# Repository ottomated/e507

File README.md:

- [Part choices & planning](./docs/Parts.md)

- Datasheets, symbols, footprints, 3d models, and spice models are in the respective folders in `./parts`

## Schematics

### Power

### MCU

### Audio

### Root

## PCB

### Rendered

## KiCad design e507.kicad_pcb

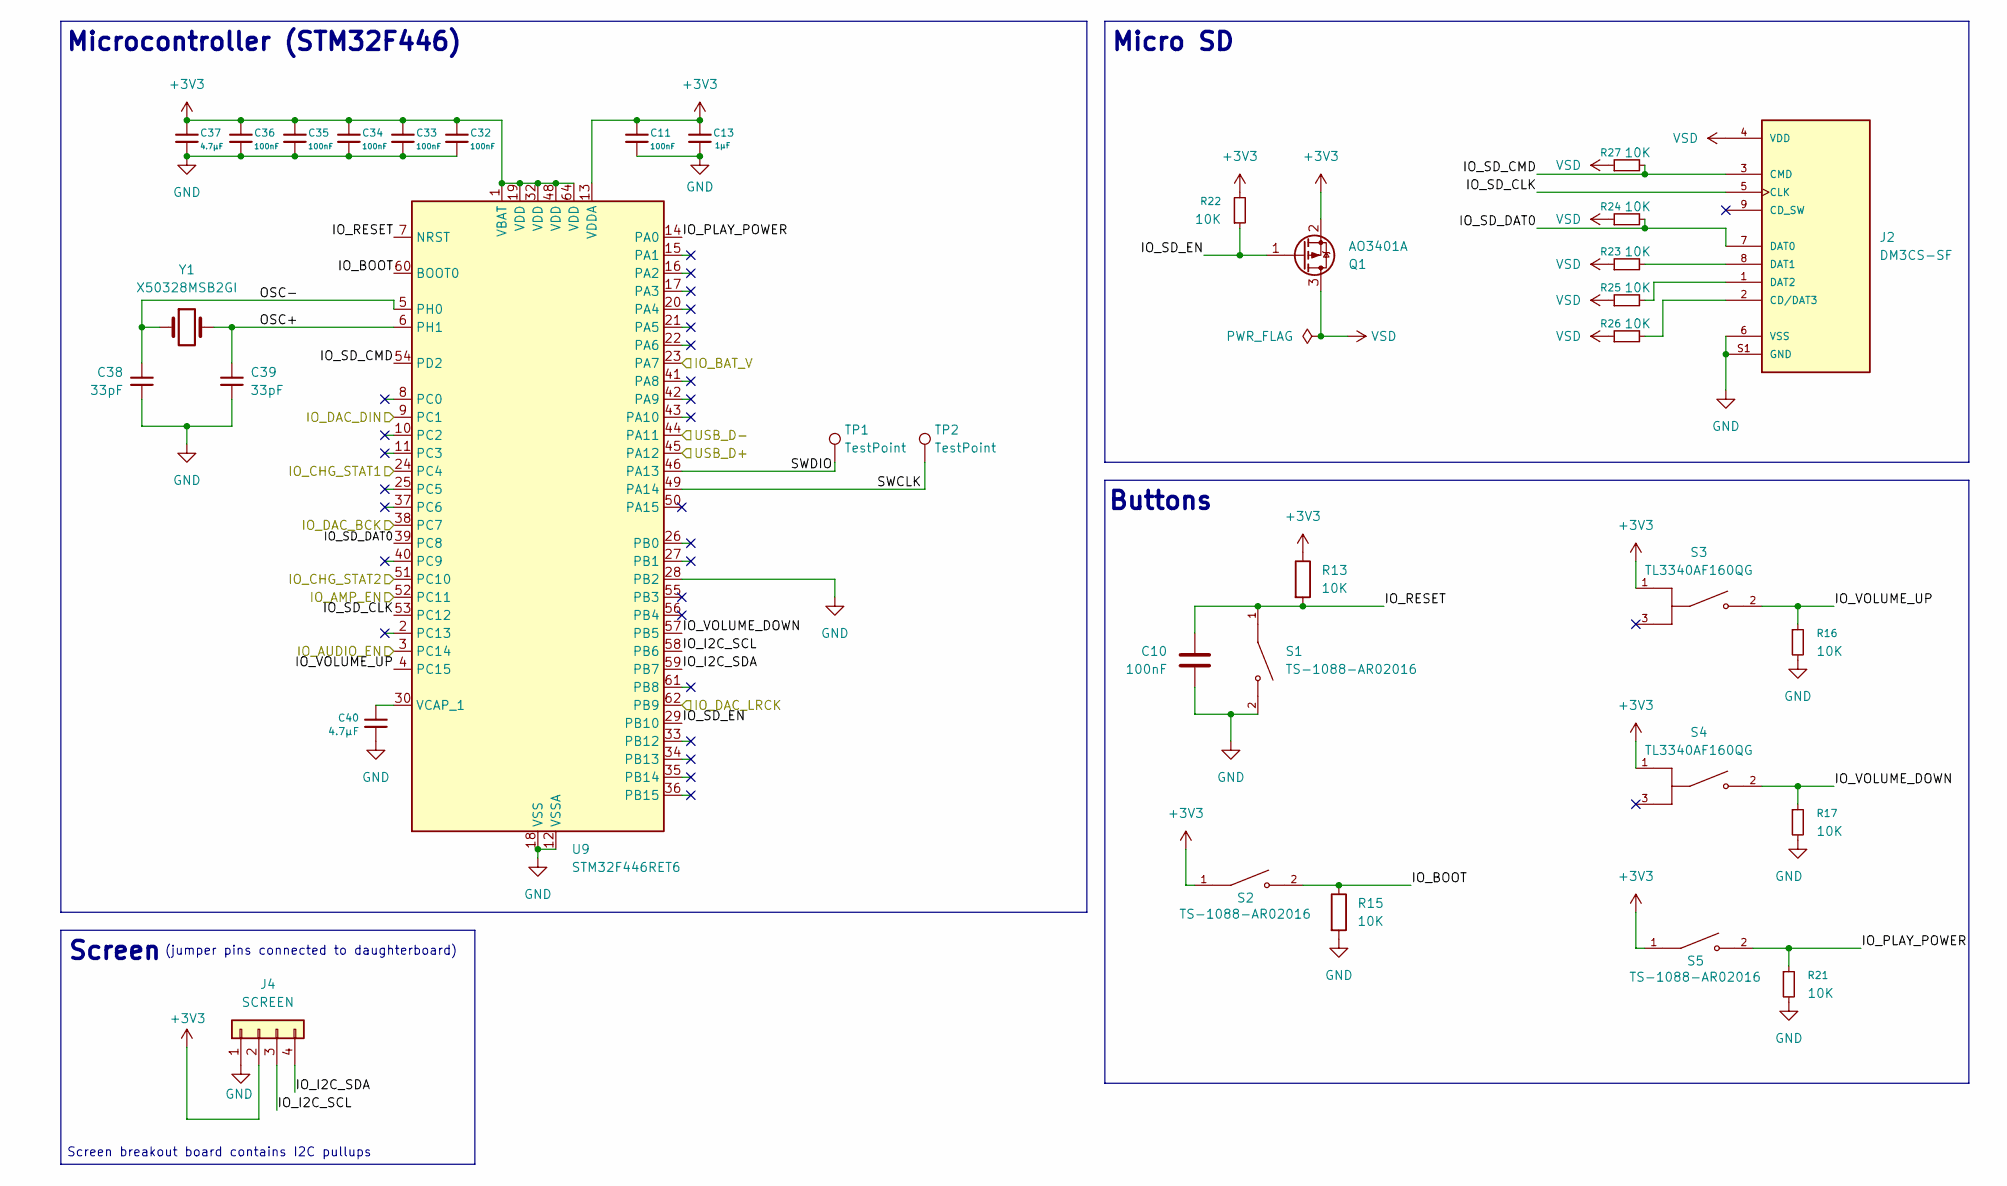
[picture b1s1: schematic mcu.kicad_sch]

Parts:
C10, C11, C32, C33, C34, C35, C36: 100nF; C_0402_1005Metric; Part # CL05B104KO5NNNC; LCSC Part # C1525
C13: 1µF; C_0603_1608Metric; Part # CL10A105KB8NNNC; LCSC Part # C15849
C37, C40: 4.7µF; C_0402_1005Metric; Part # CL05A475MP5NRNC; LCSC Part # C23733
C38, C39: 33pF; C_0402_1005Metric; Part # 0402CG330J500NT; LCSC Part # C1562
J2: DM3CS-SF; HRS_DM3CS-SF; PARTREV n/a; LCSC Part # C202111
J4: SCREEN; PinHeader_1x04_P2.54mm_Vertical; Part # 2.54-1*4; LCSC Part # C5116483
Q1: AO3401A; SOT-23; Part # AO3401A; LCSC Part # C15127
R13, R15, R16, R17, R21, R22, R23, R24, R25, R26, R27: 10K; R_0402_1005Metric; Part # 0402WGF1002TCE; LCSC Part # C25744
S1, S2, S5: TS-1088-AR02016; SW_TS-1088-AR02016; PARTREV N/A; LCSC Part # C720477
S3, S4: TL3340AF160QG; SW_TL3340AF160QG; Part # TL3340AF160QG; LCSC Part # C2886925
TP1, TP2: TestPoint; TestPoint_Pad_1.0x1.0mm
U9: STM32F446RET6; LQFP-64_10x10mm_P0.5mm; Part # STM32F446RET6; LCSC Part # C69336
Y1: X50328MSB2GI; Crystal_SMD_5032-2Pin_5.0x3.2mm; Part # X50328MSB2GI; LCSC Part # C115962

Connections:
+3V3: C11.1, C13.2, C32.1, C33.1, C34.1, C35.1, C36.1, C37.1, J4.2, Q1.2 (S), R13.1, R22.2, S2.1, S3.1, S4.1, S5.1, U9.1 (VBAT), U9.13 (VDDA), U9.19 (VDD), U9.32 (VDD), U9.48 (VDD), U9.64 (VDD); also elsewhere on the board
/Audio/IO_AMP_EN: U9.52 (PC11); also elsewhere on the board
/Audio/IO_DAC_BCK: U9.38 (PC7); also elsewhere on the board
/Audio/IO_DAC_DIN: U9.9 (PC1); also elsewhere on the board
/Audio/IO_DAC_LRCK: U9.62 (PB9); also elsewhere on the board
/MCU/IO_AUDIO_EN: U9.3 (PC14); also elsewhere on the board
/MCU/IO_BAT_V: U9.23 (PA7); also elsewhere on the board
/MCU/IO_BOOT: R15.1, S2.2, U9.60 (BOOT0)
/MCU/IO_CHG_STAT1: U9.24 (PC4); also elsewhere on the board
/MCU/IO_CHG_STAT2: U9.51 (PC10); also elsewhere on the board
/MCU/IO_I2C_SCL: J4.3, U9.58 (PB6)
/MCU/IO_I2C_SDA: J4.4, U9.59 (PB7)
/MCU/IO_PLAY_POWER: R21.1, S5.2, U9.14 (PA0)
/MCU/IO_RESET: C10.1, R13.2, S1.1, U9.7 (NRST)
/MCU/IO_SD_CLK: J2.5 (CLK), U9.53 (PC12)
/MCU/IO_SD_CMD: J2.3 (CMD), R27.2, U9.54 (PD2)
/MCU/IO_SD_DAT0: J2.7 (DAT0), R24.2, U9.39 (PC8)
/MCU/IO_SD_EN: Q1.1 (G), R22.1, U9.29 (PB10)
/MCU/IO_VOLUME_DOWN: R17.1, S4.2, U9.57 (PB5)
/MCU/IO_VOLUME_UP: R16.1, S3.2, U9.4 (PC15)
/MCU/OSC+: C39.1, U9.6 (PH1), Y1.2
/MCU/OSC-: C38.1, U9.5 (PH0), Y1.1
/MCU/SWCLK: TP2.1 (1_1), U9.49 (PA14)
/MCU/SWDIO: TP1.1 (1_1), U9.46 (PA13)
/MCU/USB_D+: U9.45 (PA12); also elsewhere on the board
/MCU/USB_D-: U9.44 (PA11); also elsewhere on the board
GND: C10.2, C11.2, C13.1, C32.2, C33.2, C34.2, C35.2, C36.2, C37.2, C38.2, C39.2, C40.2, J2.6 (VSS), J2.S1 (GND), J2.S2 (GND), J2.S3 (GND), J2.S5 (GND), J4.1, R15.2, R16.2, R17.2, R21.2, S1.2, U9.12 (VSSA), U9.18 (VSS), U9.28 (PB2), U9.31 (VSS), U9.47 (VSS), U9.63 (VSS); also elsewhere on the board
unnamed: J2.2 (CD/DAT3), R26.2
unnamed: J2.8 (DAT1), R23.2
unnamed: J2.1 (DAT2), R25.2
unnamed: C40.1, U9.30 (VCAP_1)
VSD: J2.4 (VDD), Q1.3 (D), R23.1, R24.1, R25.1, R26.1, R27.1

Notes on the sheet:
(jumper pins connected to daughterboard)
Micro SD
Buttons
Screen breakout board contains I2C pullups
Microcontroller (STM32F446)
Screen

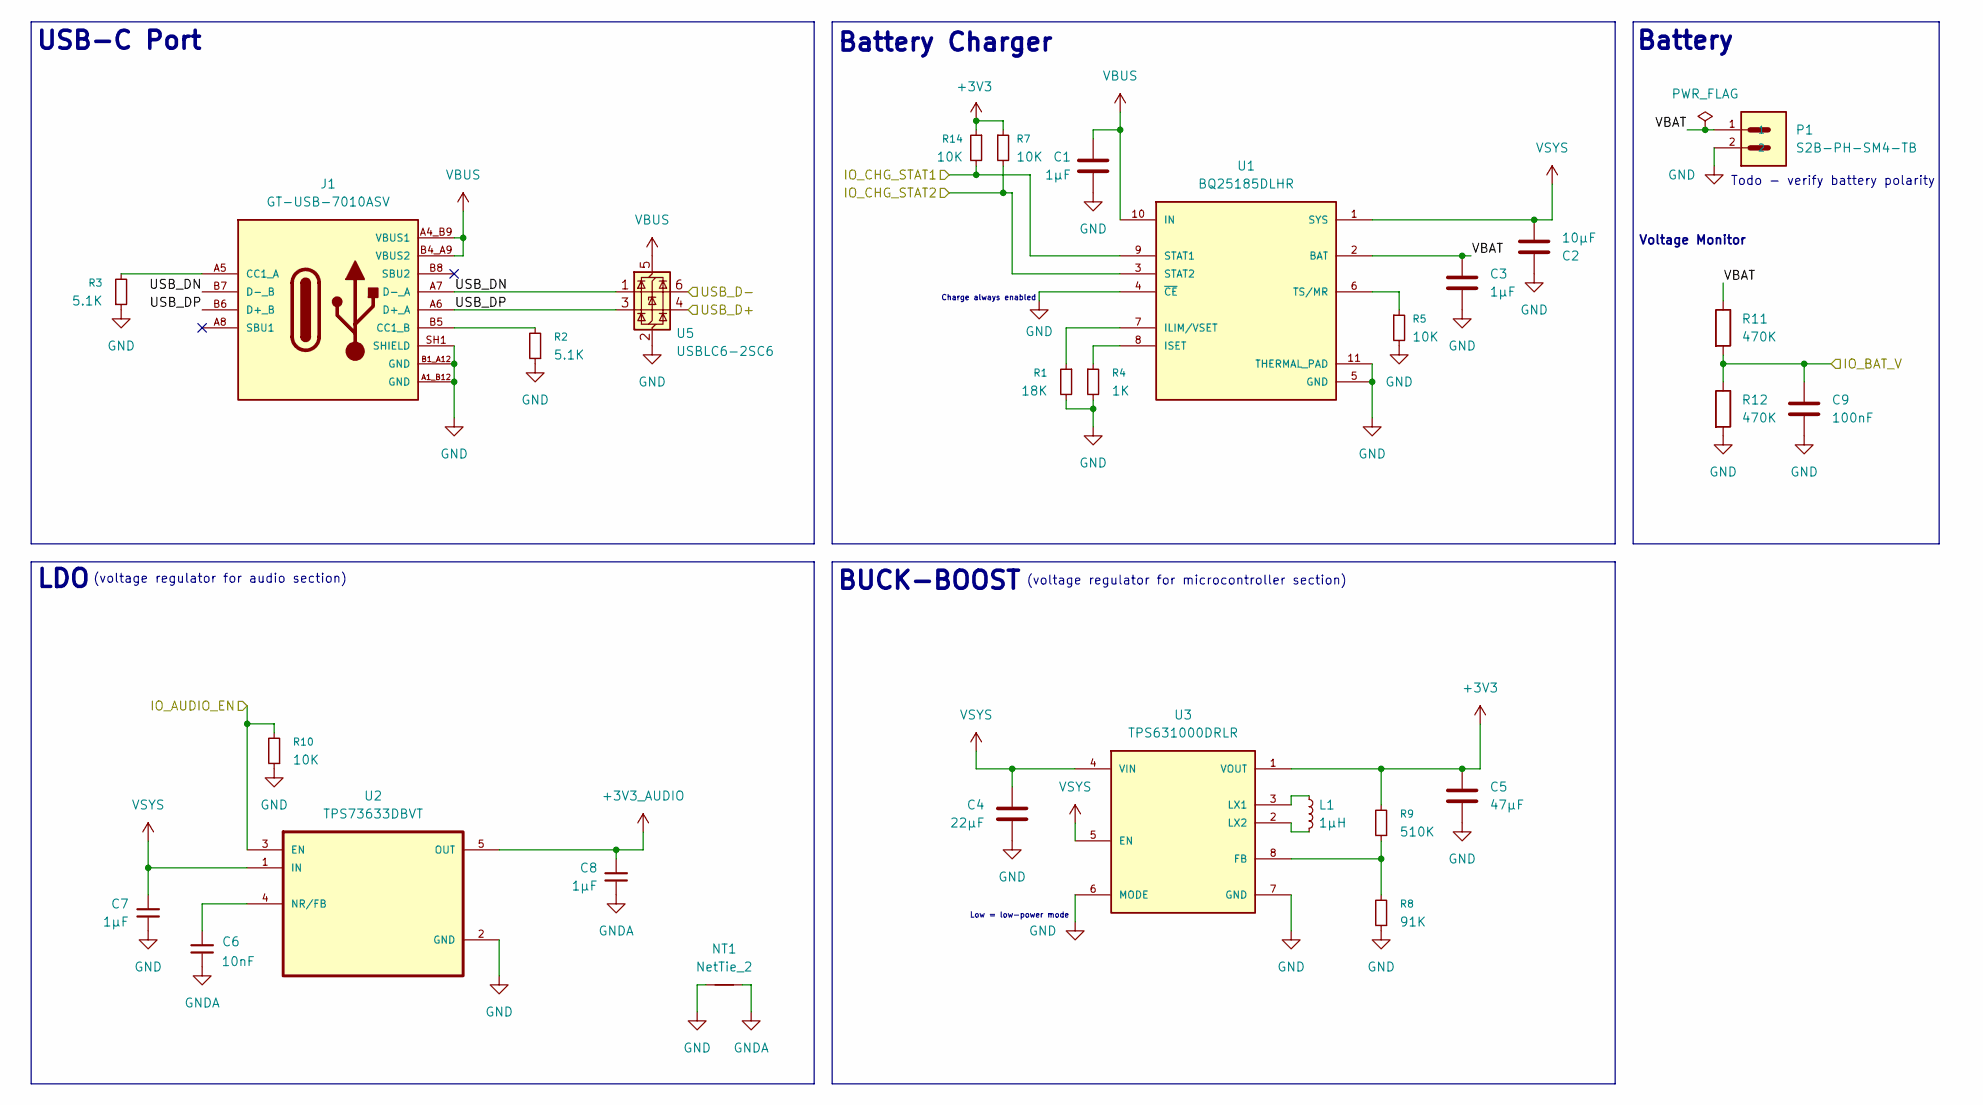
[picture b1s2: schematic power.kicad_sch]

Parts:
C1, C3: 1µF; C_0603_1608Metric; Part # CL10A105KB8NNNC; LCSC Part # C15849
C2: 10µF; C_0603_1608Metric; Part # CL10A106MA8NRNC; LCSC Part # C96446
C4: 22µF; C_0603_1608Metric; Part # CL10A226MQ8NRNC; LCSC Part # C59461
C5: 47µF; C_0805_2012Metric; Part # CL21A476MQYNNNE; LCSC Part # C16780
C6: 10nF; C_0402_1005Metric; Part # CL05B103KB5NNNC; LCSC Part # C15195
C7, C8: 1µF; C_0402_1005Metric; Part # CL05A105KA5NQNC; LCSC Part # C52923
C9: 100nF; C_0402_1005Metric; Part # CL05B104KO5NNNC; LCSC Part # C1525
J1: GT-USB-7010ASV; AMPHENOL_12402012E212A; PARTREV 4; LCSC Part # C2988369
L1: 1μH; L_1008_2520Metric; Part # DFE252012P-1R0M=P2; LCSC Part # C882955
NT1: NetTie_2; NetTie-2_SMD_Pad0.5mm
P1: S2B-PH-SM4-TB; JST_S2B-PH-SM4-TB; Part # XY-S2B-PH-SM4-TB; LCSC Part # C54582899
R1: 18K; R_0402_1005Metric; Part # 0402WGF1802TCE; LCSC Part # C25762
R2, R3: 5.1K; R_0402_1005Metric; Part # 0402WGF5101TCE; LCSC Part # C25905
R4: 1K; R_0402_1005Metric; Part # 0402WGF1001TCE; LCSC Part # C11702
R5, R7, R10, R14: 10K; R_0402_1005Metric; Part # 0402WGF1002TCE; LCSC Part # C25744
R8: 91K; R_0603_1608Metric; Part # 0603WAF9102T5E; LCSC Part # C23265
R9: 510K; R_0603_1608Metric; Part # 0603WAF5103T5E; LCSC Part # C23192
R11: 470K; R_0402_1005Metric; LCSC Part # C25790
R12: 470K; R_0402_1005Metric; Part # 0603WAF4703T5E; LCSC Part # C25790
U1: BQ25185DLHR; IC_BQ25185DLHR; PARTREV OCTOBER 2023; LCSC Part # C19725033
U2: TPS73633DBVT; SOT95P280X145-5N; Part # TPS73633DBVT; LCSC Part # C2864221
U3: TPS631000DRLR; SOT-583-8; PARTREV B; LCSC Part # C5219190
U5: USBLC6-2SC6; SOT-23-6; Part # ST USBLC6-2SC6; LCSC Part # C7519

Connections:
+3V3: C5.2, R7.1, R9.2, R14.1, U3.1 (VOUT); also elsewhere on the board
+3V3_AUDIO: C8.1, U2.5 (OUT); also elsewhere on the board
/MCU/IO_AUDIO_EN: R10.2, U2.3 (EN); also elsewhere on the board
/MCU/IO_BAT_V: C9.1, R11.2, R12.1; also elsewhere on the board
/MCU/IO_CHG_STAT1: R14.2, U1.9 (STAT1); also elsewhere on the board
/MCU/IO_CHG_STAT2: R7.2, U1.3 (STAT2); also elsewhere on the board
/MCU/USB_D+: U5.4 (I/O2); also elsewhere on the board
/MCU/USB_D-: U5.6 (I/O1); also elsewhere on the board
/Power/USB_DN: J1.A7 (D-_A), J1.B7 (D-_B), U5.1 (I/O1)
/Power/USB_DP: J1.A6 (D+_A), J1.B6 (D+_B), U5.3 (I/O2)
/Power/VBAT: C3.2, P1.1, R11.1, U1.2 (BAT)
GND: C1.1, C2.2, C3.1, C4.1, C5.1, C7.1, C9.2, J1.A1_B12 (GND), J1.B1_A12 (GND), J1.SH1 (SHIELD), J1.SH2 (SHIELD), J1.SH3 (SHIELD), J1.SH4 (SHIELD), NT1.1, P1.2, R1.2, R2.1, R3.1, R4.2, R5.2, R8.1, R10.1, R12.2, U1.4 (~CE), U1.5 (GND), U1.11 (THERMAL_PAD), U1.12, U1.13, U2.2 (GND), U3.6 (MODE), U3.7 (GND), U5.2 (GND); also elsewhere on the board
GNDA: C6.1, C8.2, NT1.2; also elsewhere on the board
unnamed: J1.A5 (CC1_A), R3.2
unnamed: J1.B5 (CC1_B), R2.2
unnamed: R1.1, U1.7 (ILIM/VSET)
unnamed: R4.1, U1.8 (ISET)
unnamed: R5.1, U1.6 (TS/MR)
unnamed: C6.2, U2.4 (NR/FB)
unnamed: R8.2, R9.1, U3.8 (FB)
unnamed: L1.1, U3.3 (LX1)
unnamed: L1.2, U3.2 (LX2)
VBUS: C1.2, J1.A4_B9 (VBUS1), J1.B4_A9 (VBUS), U1.10 (IN), U5.5 (VBUS)
VSYS: C2.1, C4.2, C7.2, U1.1 (SYS), U2.1 (IN), U3.4 (VIN), U3.5 (EN)

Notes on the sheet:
Charge always enabled
Battery Charger
(voltage regulator for microcontroller section)
Low = low-power mode
USB-C Port
Todo - verify battery polarity
(voltage regulator for audio section)
Battery
Voltage Monitor
LDO
BUCK-BOOST

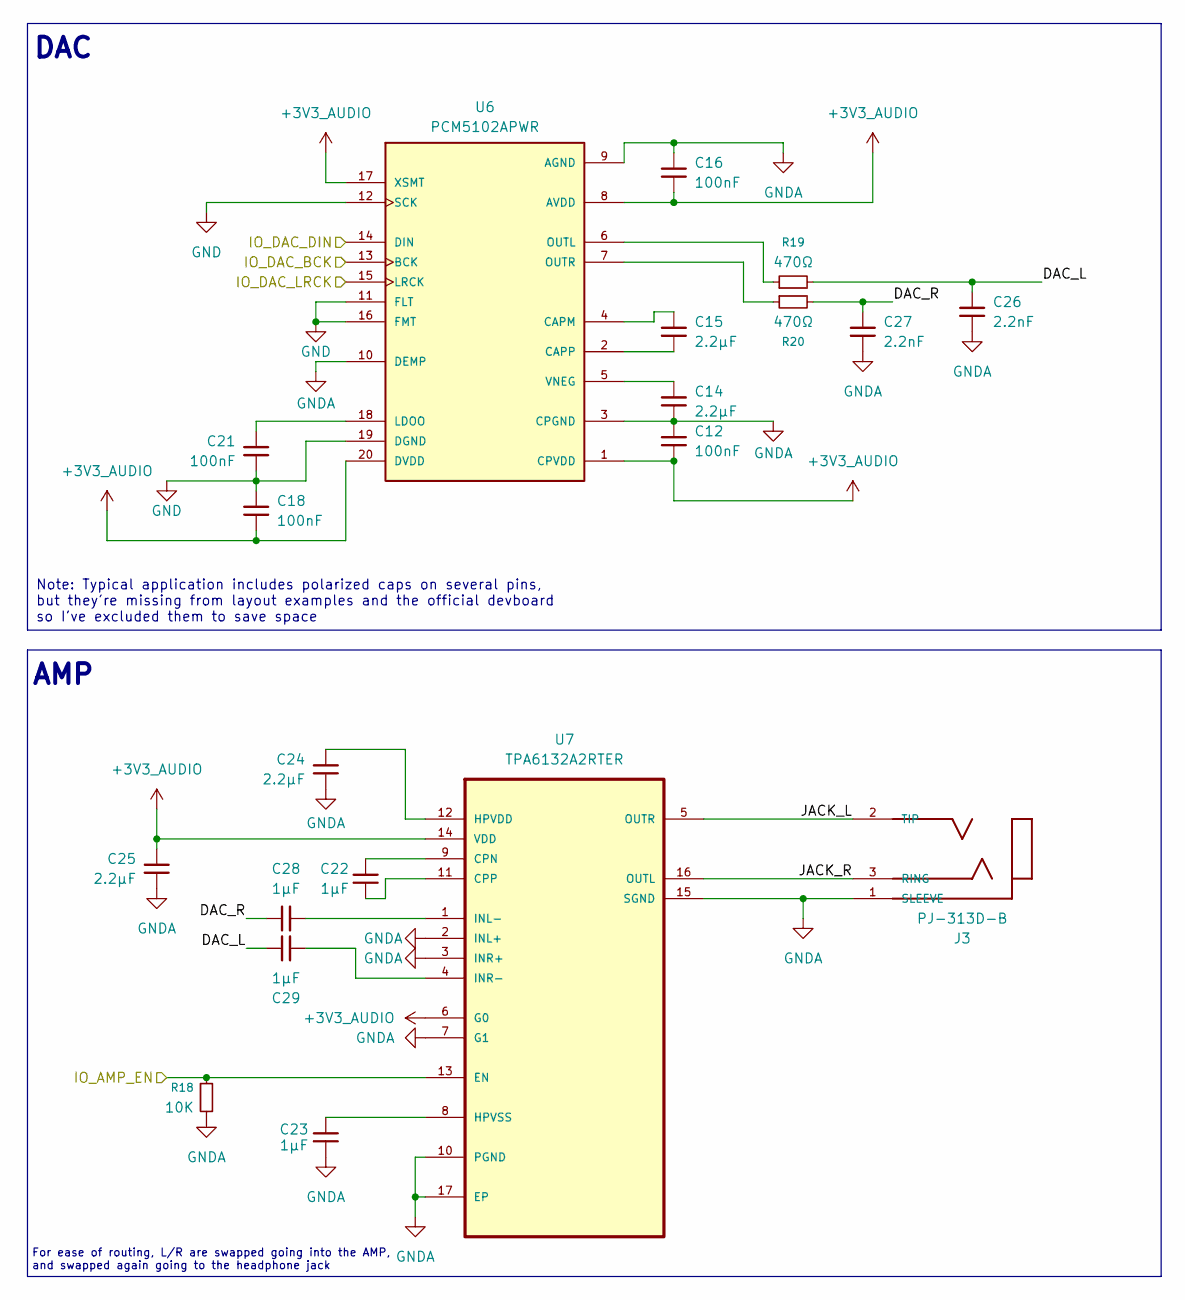
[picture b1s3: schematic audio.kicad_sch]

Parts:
C12, C16, C18, C21: 100nF; C_0402_1005Metric; Part # CL05B104KB54PNC; LCSC Part # C307331
C14, C15, C24, C25: 2.2µF; C_0402_1005Metric; Part # CL05A225MQ5NSNC; LCSC Part # C12530
C22, C23, C28, C29: 1µF; C_0402_1005Metric; Part # CL05A105KA5NQNC; LCSC Part # C52923
C26, C27: 2.2nF; C_0603_1608Metric; Part # 0603B222K500NT; LCSC Part # C1604
J3: PJ-313D-B; PJ-3135-B; Part # PJ-313D-B; LCSC Part # C319112
R18: 10K; R_0402_1005Metric; Part # 0402WGF1002TCE; LCSC Part # C25744
R19, R20: 470Ω; R_0402_1005Metric; Part # 0402WGF4700TCE; LCSC Part # C25117
U6: PCM5102APWR; SOP65P640X120-20N; PARTREV C; LCSC Part # C107671
U7: TPA6132A2RTER; WQFN-16-1EP_3x3mm_P0.5mm_EP1.6x1.6mm_ThermalVias; MPN TPA6132A2RTER; LCSC Part # C69901

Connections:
+3V3_AUDIO: C12.2, C16.2, C18.2, C25.1, U6.1 (CPVDD), U6.8 (AVDD), U6.17 (XSMT), U6.20 (DVDD), U7.6 (G0), U7.14 (VDD); also elsewhere on the board
/Audio/DAC_L: C26.1, C29.1, R19.2
/Audio/DAC_R: C27.1, C28.1, R20.2
/Audio/IO_AMP_EN: R18.1, U7.13 (EN); also elsewhere on the board
/Audio/IO_DAC_BCK: U6.13 (BCK); also elsewhere on the board
/Audio/IO_DAC_DIN: U6.14 (DIN); also elsewhere on the board
/Audio/IO_DAC_LRCK: U6.15 (LRCK); also elsewhere on the board
/Audio/JACK_L: J3.2 (TIP), U7.5 (OUTR)
/Audio/JACK_R: J3.3 (RING), U7.16 (OUTL)
GND: C18.1, C21.2, U6.11 (FLT), U6.12 (SCK), U6.16 (FMT), U6.19 (DGND); also elsewhere on the board
GNDA: C12.1, C14.2, C16.1, C23.1, C24.2, C25.2, C26.2, C27.2, J3.1 (SLEEVE), R18.2, U6.3 (CPGND), U6.9 (AGND), U6.10 (DEMP), U7.2 (INL+), U7.3 (INR+), U7.7 (G1), U7.10 (PGND), U7.15 (SGND), U7.17 (EP); also elsewhere on the board
unnamed: C15.1, U6.4 (CAPM)
unnamed: C15.2, U6.2 (CAPP)
unnamed: C21.1, U6.18 (LDOO)
unnamed: R19.1, U6.6 (OUTL)
unnamed: R20.1, U6.7 (OUTR)
unnamed: C14.1, U6.5 (VNEG)
unnamed: C22.1, U7.9 (CPN)
unnamed: C22.2, U7.11 (CPP)
unnamed: C24.1, U7.12 (HPVDD)
unnamed: C23.2, U7.8 (HPVSS)
unnamed: C28.2, U7.1 (INL-)
unnamed: C29.2, U7.4 (INR-)

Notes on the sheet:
Note: Typical application includes polarized caps on several pins, but they're missing from layout examples and the official devboard so I've excluded them to save space
DAC
For ease of routing, L/R are swapped going into the AMP, and swapped again going to the headphone jack
AMP

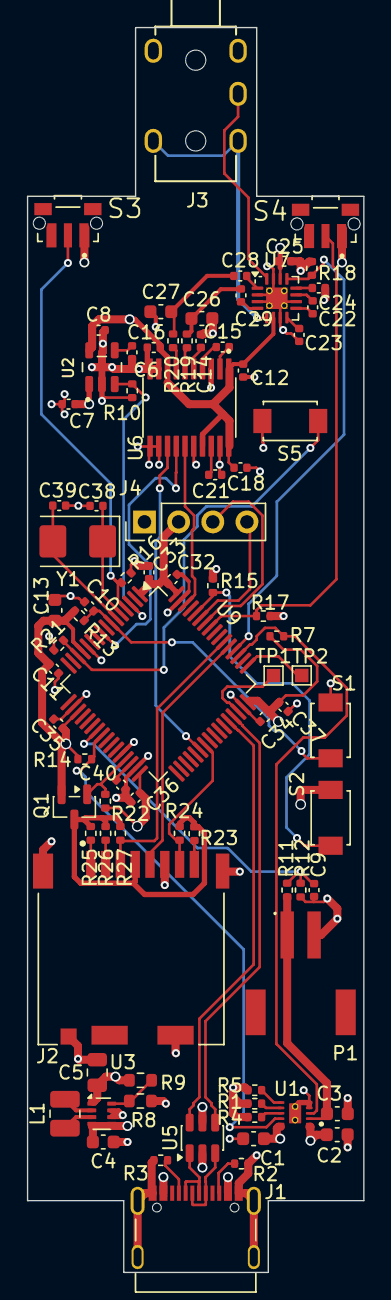
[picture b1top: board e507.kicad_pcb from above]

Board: 4 copper layers, 25.0 x 92.5 mm, 84 parts (0 on the bottom side), 64 nets.
